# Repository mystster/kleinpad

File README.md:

# kleinpad
This is a small, self-made keyboard with a limited number of keys, designed by mystster.

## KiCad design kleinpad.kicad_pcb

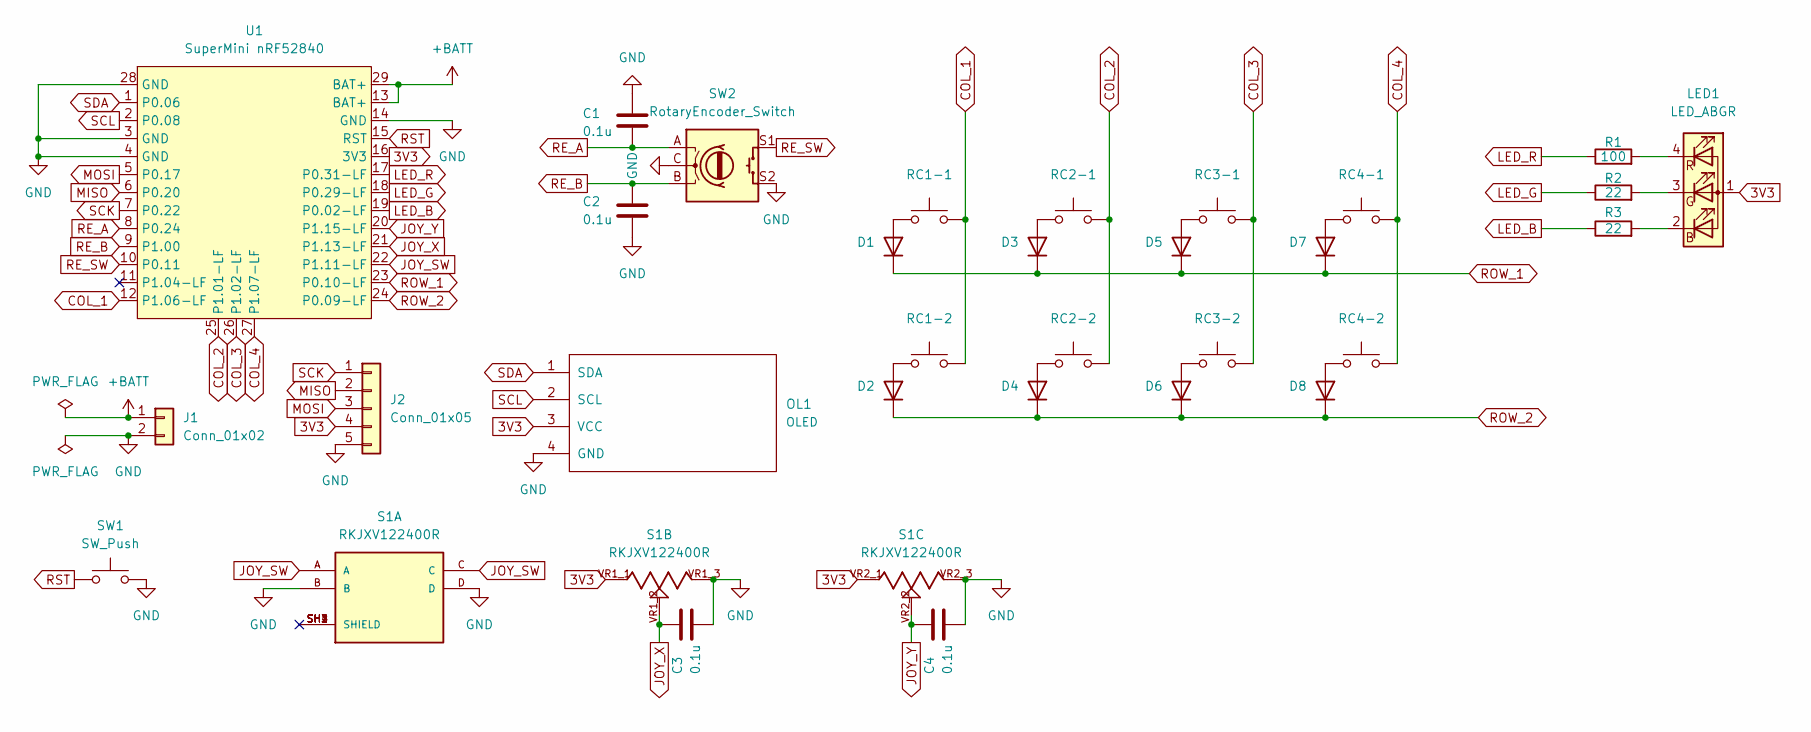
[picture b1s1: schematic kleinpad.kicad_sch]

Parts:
C1, C2, C3, C4: 0.1u; C_Disc_D3.8mm_W2.6mm_P2.50mm
D1, D2, D3, D4, D5, D6, D7, D8: 1N4148; Diode_TH_SMD
J1: Conn_01x02; JST_PH_S2B-PH-K_1x02_P2.00mm_Horizontal
J2: Conn_01x05; PinHeader_1x05_P2.54mm_Horizontal
LED1: LED_ABGR; LED Rectangle(OSTBMAZ2C1D)
OL1: OLED
R1: 100; Resistor-Compact-1-side
R2, R3: 22; Resistor-Compact-1-side
RC1-1, RC1-2, RC2-1, RC2-2, RC3-1, RC3-2, RC4-1, RC4-2: SW_Push; CherryMX_Hotswap_1u
S1: RKJXV122400R; SW_RKJXV122400R; PARTREV N/A
SW1: SW_Push; ResetSW
SW2: RotaryEncoder_Switch; RotaryEncoder_EC11
U1: SuperMini nRF52840; SuperMini_nRF52840_AH_USBup

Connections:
3V3: J2.4, LED1.1 (A), OL1.3 (VCC), S1.VR1_1, S1.VR2_1, U1.16 (3V3)
+BATT: J1.1, U1.13 (BAT+), U1.29 (BAT+)
COL_1: RC1-1.1, RC1-2.1, U1.12 (P1.06-LF)
COL_2: RC2-1.1, RC2-2.1, U1.25 (P1.01-LF)
COL_3: RC3-1.1, RC3-2.1, U1.26 (P1.02-LF)
COL_4: RC4-1.1, RC4-2.1, U1.27 (P1.07-LF)
GND: C1.1, C2.2, C3.2, C4.2, J1.2, J2.5, OL1.4 (GND), S1.B, S1.D, S1.VR1_3, S1.VR2_3, SW1.2, SW2.C, SW2.S2, U1.3 (GND), U1.4 (GND), U1.14 (GND), U1.28 (GND)
JOY_SW: S1.A, S1.C, U1.22 (P1.11-LF)
JOY_X: C3.1, S1.VR1_2, U1.21 (P1.13-LF)
JOY_Y: C4.1, S1.VR2_2, U1.20 (P1.15-LF)
LED_B: R3.1, U1.19 (P0.02-LF)
LED_G: R2.1, U1.18 (P0.29-LF)
LED_R: R1.1, U1.17 (P0.31-LF)
MISO: J2.2, U1.6 (P0.20)
MOSI: J2.3, U1.5 (P0.17)
unnamed: D1.2 (A), RC1-1.2
unnamed: D2.2 (A), RC1-2.2
unnamed: D3.2 (A), RC2-1.2
unnamed: D4.2 (A), RC2-2.2
unnamed: D5.2 (A), RC3-1.2
unnamed: D6.2 (A), RC3-2.2
unnamed: D7.2 (A), RC4-1.2
unnamed: D8.2 (A), RC4-2.2
unnamed: LED1.2 (BK), R3.2
unnamed: LED1.3 (GK), R2.2
unnamed: LED1.4 (RK), R1.2
RE_A: C1.2, SW2.A, U1.8 (P0.24)
RE_B: C2.1, SW2.B, U1.9 (P1.00)
RE_SW: SW2.S1, U1.10 (P0.11)
ROW_1: D1.1 (K), D3.1 (K), D5.1 (K), D7.1 (K), U1.23 (P0.10-LF)
ROW_2: D2.1 (K), D4.1 (K), D6.1 (K), D8.1 (K), U1.24 (P0.09-LF)
RST: SW1.1, U1.15 (RST)
SCK: J2.1, U1.7 (P0.22)
SCL: OL1.2 (SCL), U1.2 (P0.08)
SDA: OL1.1 (SDA), U1.1 (P0.06)

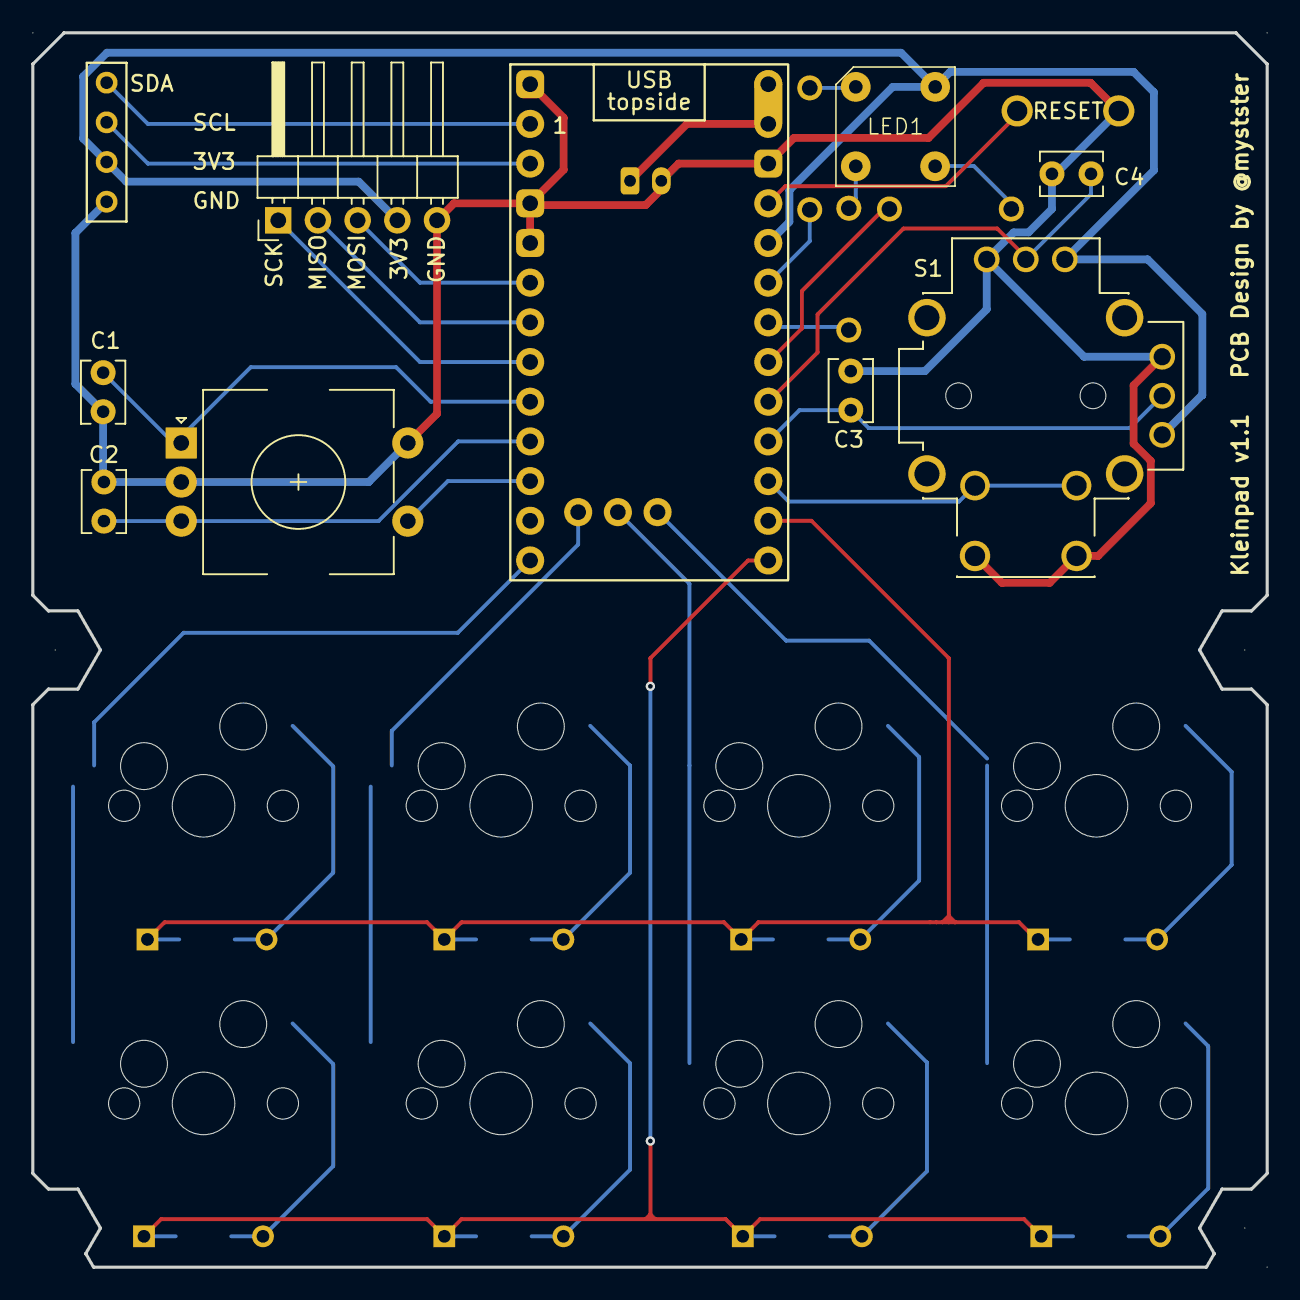
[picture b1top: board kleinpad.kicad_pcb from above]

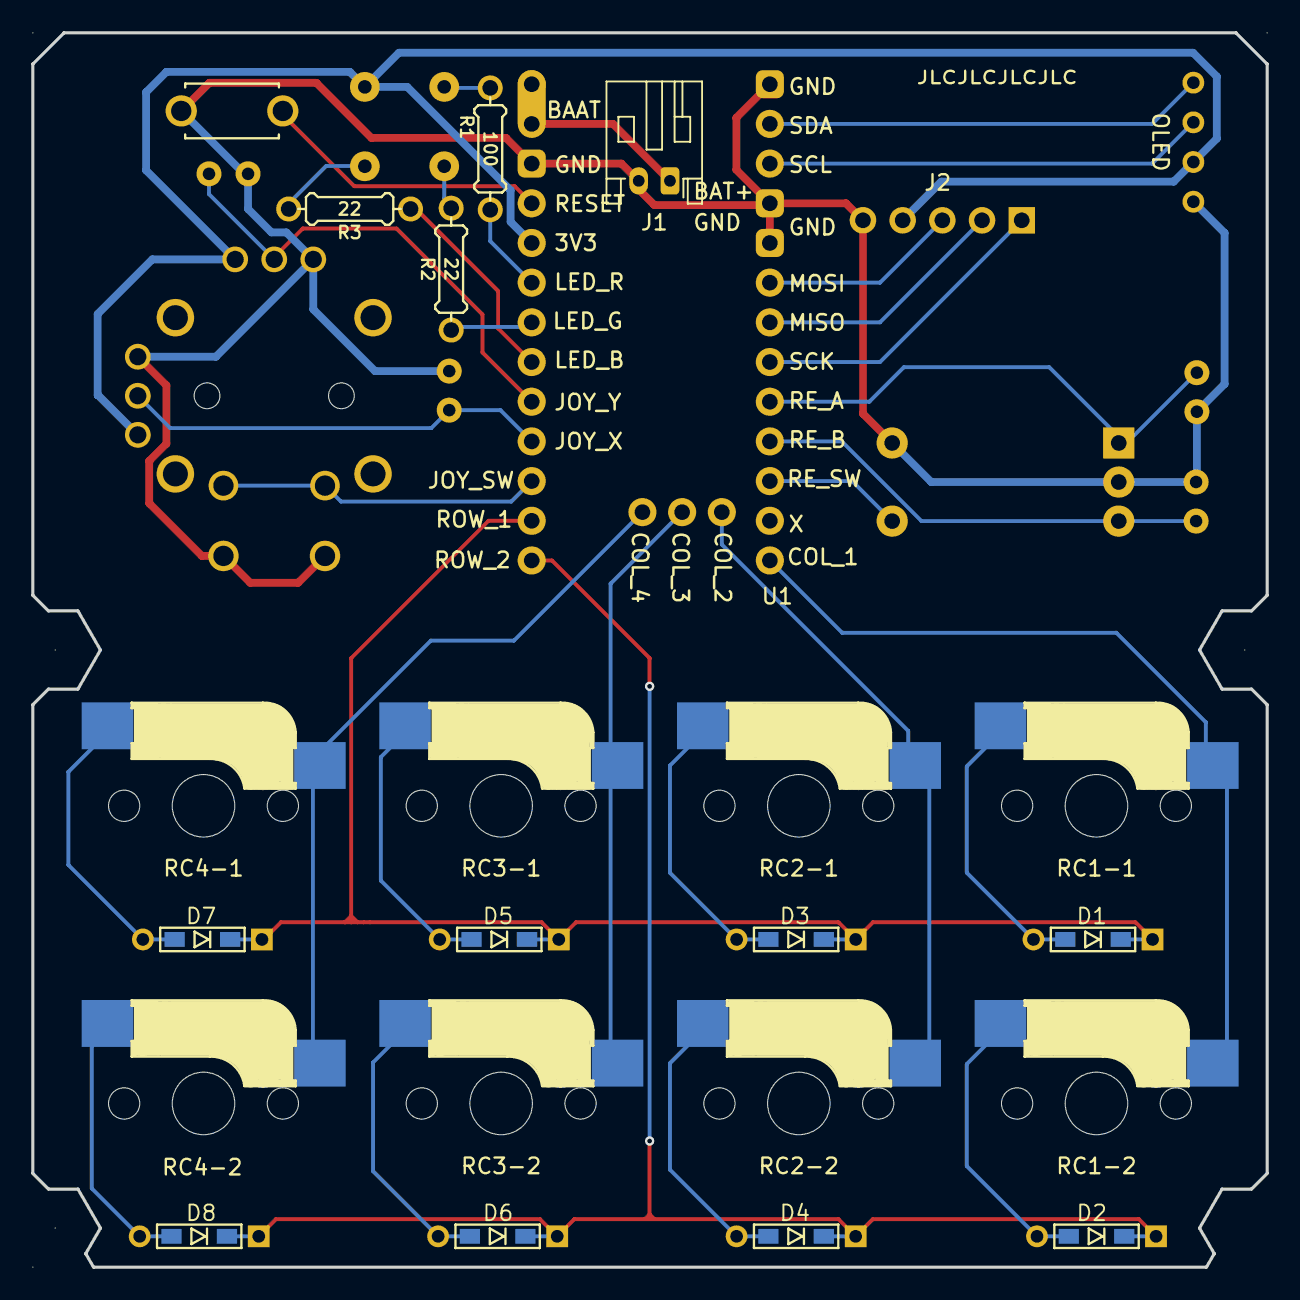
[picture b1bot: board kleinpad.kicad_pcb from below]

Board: 2 copper layers, 79.0 x 79.0 mm, 31 parts (4 on the bottom side), 35 nets.

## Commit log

2025-06-28 feat: Add initial KiCad schematic and PCB project files
    Introduces the foundational schematic, PCB layout, and project configuration for the new hardware design. Enables schematic capture, layout, and build processes in KiCad for future hardware developme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
2025-06-29 feat: add pcb
2025-08-03 feat: 回路図を追加
2025-08-03 feat: JLCPCBへ発注
2025-08-16 fix: LEDに抵抗がない
    抵抗値は手元にあるものに合わせて変更
    Fixes #2
2025-08-16 feat: 3Dプリンタ用STL作成用のファイルを追加
2025-08-16 fix: .gitignoreにバックアップファイルのパターンを追加
2025-08-16 feat: JLCPCBへ1回目の発注を行ったファイル
2025-08-16 fix: バッテリーコネクタが接続できない Fixes #1
    commit: 14f930df53bbbcb42010b72f48aa18af7e7124dd で修正済みだった
2025-08-16 fix: 抵抗周りの配線のレイアウトを変更
2025-08-16 fix: 未接続の配線を接続
2025-08-16 feat: bump version
2025-08-22 fix: OLEDとSuperMiniの干渉 Fixes #4
2025-08-22 fix: ダイオードのスルーホールがキースイッチに干渉する Fixes #3
2025-08-22 chore: bump version
2025-08-22 feat: add jlc order place
2025-08-22 fix: 配線を少しだけ変更
2025-08-22 feat: add JLCPCB files
